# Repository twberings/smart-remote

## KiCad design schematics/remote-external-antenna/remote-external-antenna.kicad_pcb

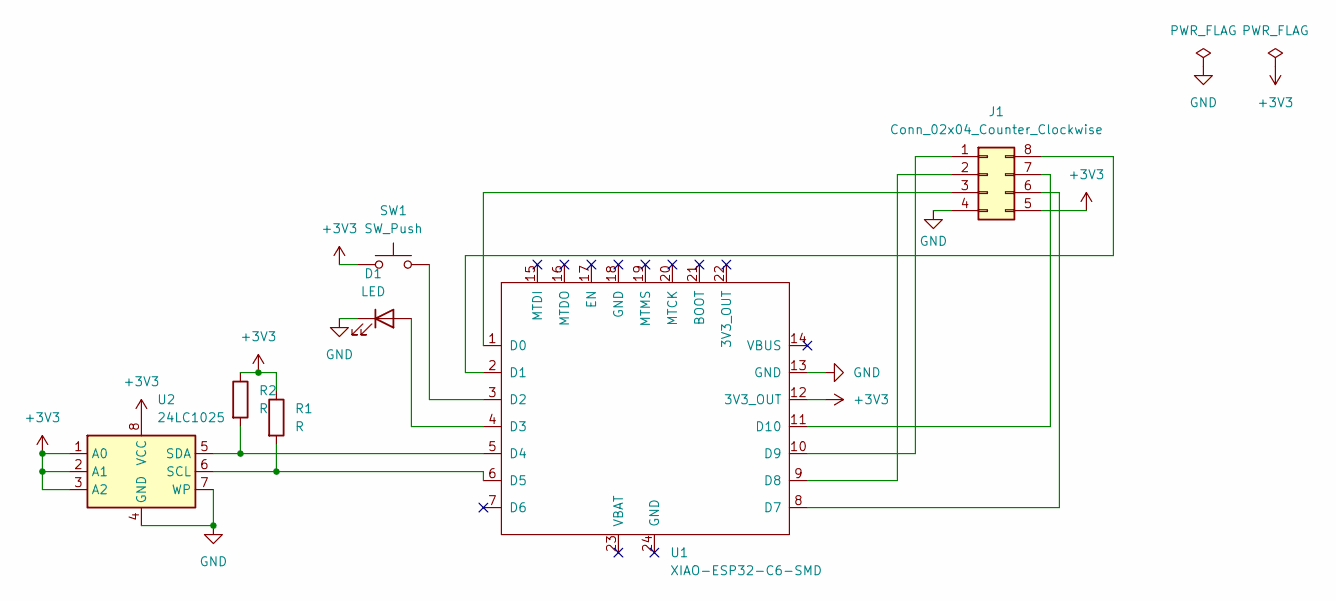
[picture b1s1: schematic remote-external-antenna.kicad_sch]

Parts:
D1: LED; TestPoint_2Pads_Pitch5.08mm_Drill1.3mm
J1: Conn_02x04_Counter_Clockwise; CC1101
R1, R2: R; R_0603_1608Metric
SW1: SW_Push; TestPoint_2Pads_Pitch5.08mm_Drill1.3mm
U1: XIAO-ESP32-C6-SMD; XIAO-ESP32-C6-DIP
U2: 24LC1025; SOIC-8_3.9x4.9mm_P1.27mm

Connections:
+3V3: J1.5, R1.1, R2.1, SW1.1, U1.12 (3V3_OUT), U2.1 (A0), U2.2 (A1), U2.3 (A2), U2.8 (VCC)
GND: D1.1 (K), J1.4, U1.13 (GND), U2.4 (GND), U2.7 (WP)
unnamed: D1.2 (A), U1.4 (D3)
unnamed: J1.1, U1.10 (D9)
unnamed: J1.2, U1.9 (D8)
unnamed: J1.3, U1.1 (D0)
unnamed: J1.6, U1.8 (D7)
unnamed: J1.7, U1.11 (D10)
unnamed: J1.8, U1.2 (D1)
unnamed: SW1.2, U1.3 (D2)
unnamed: R2.2, U1.5 (D4), U2.5 (SDA)
unnamed: R1.2, U1.6 (D5), U2.6 (SCL)

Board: 2 copper layers, 7 parts (0 on the bottom side), 12 nets, no tracks yet.
